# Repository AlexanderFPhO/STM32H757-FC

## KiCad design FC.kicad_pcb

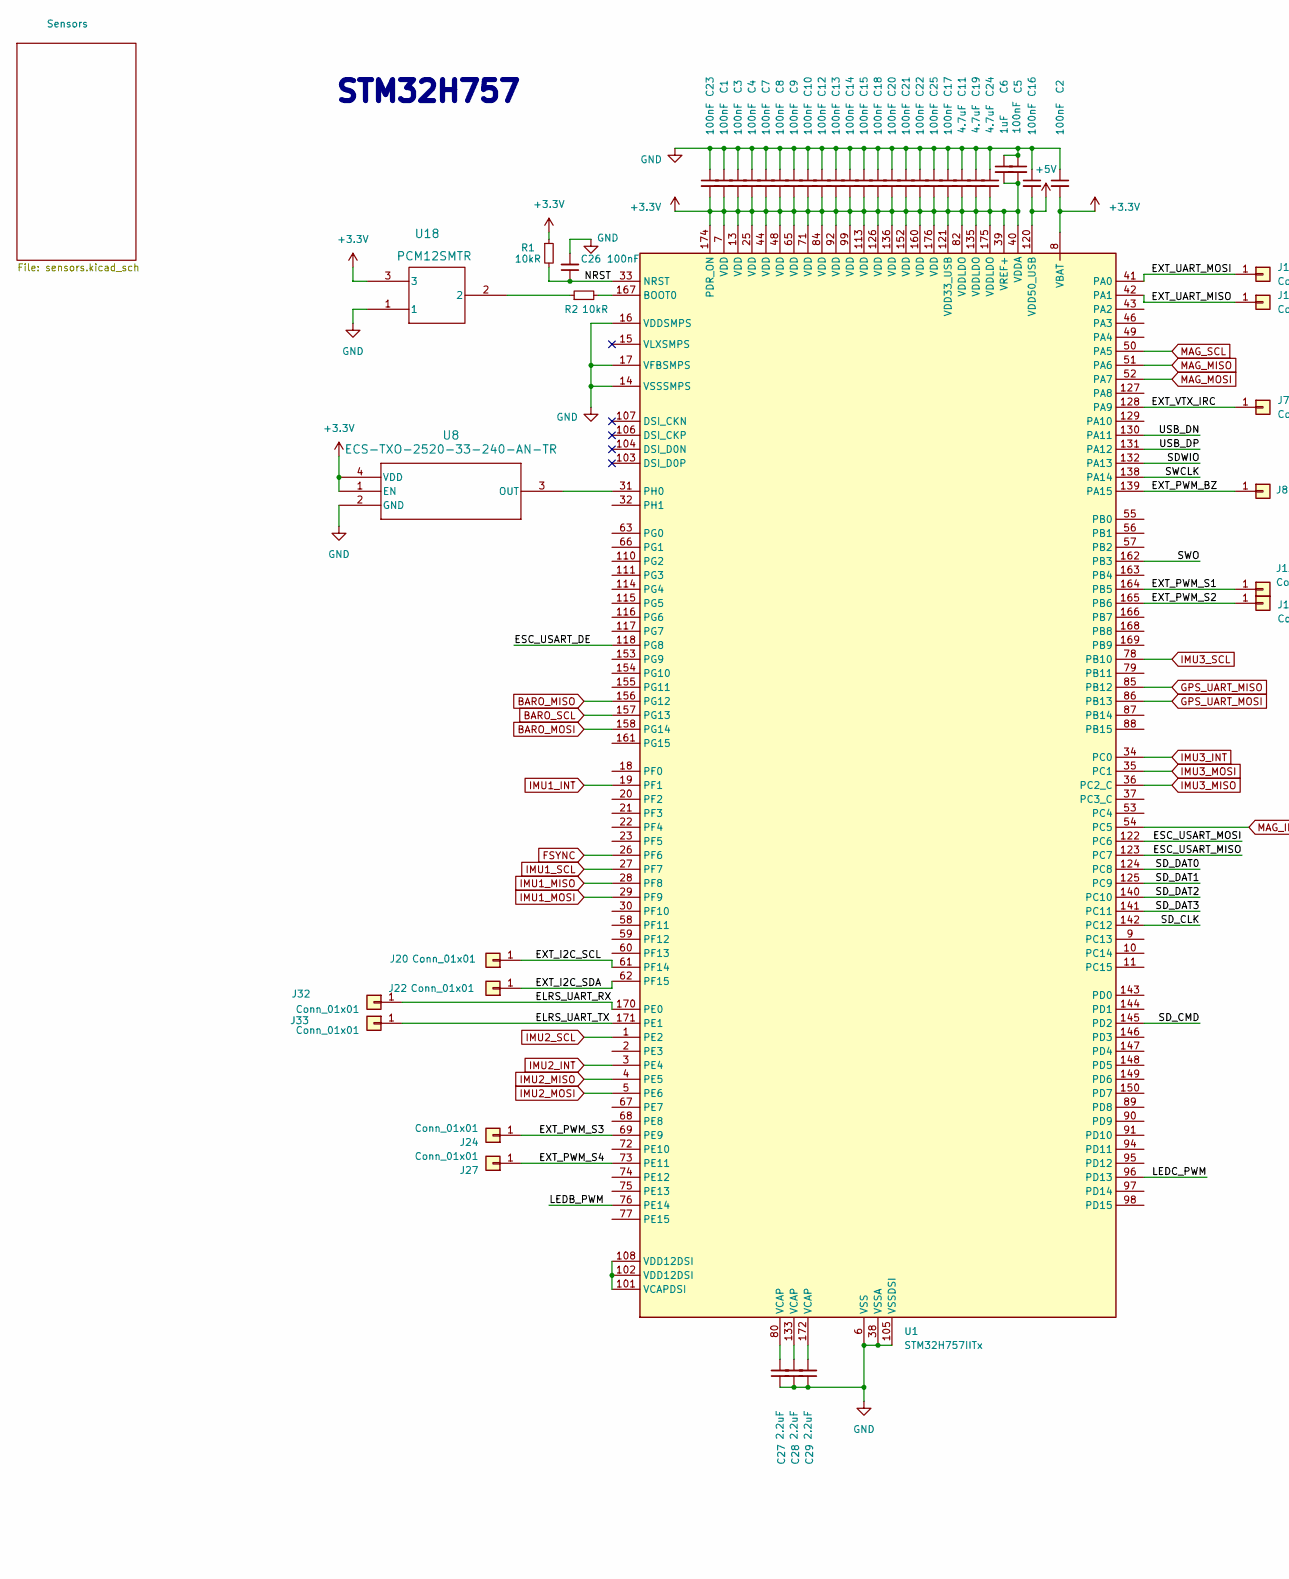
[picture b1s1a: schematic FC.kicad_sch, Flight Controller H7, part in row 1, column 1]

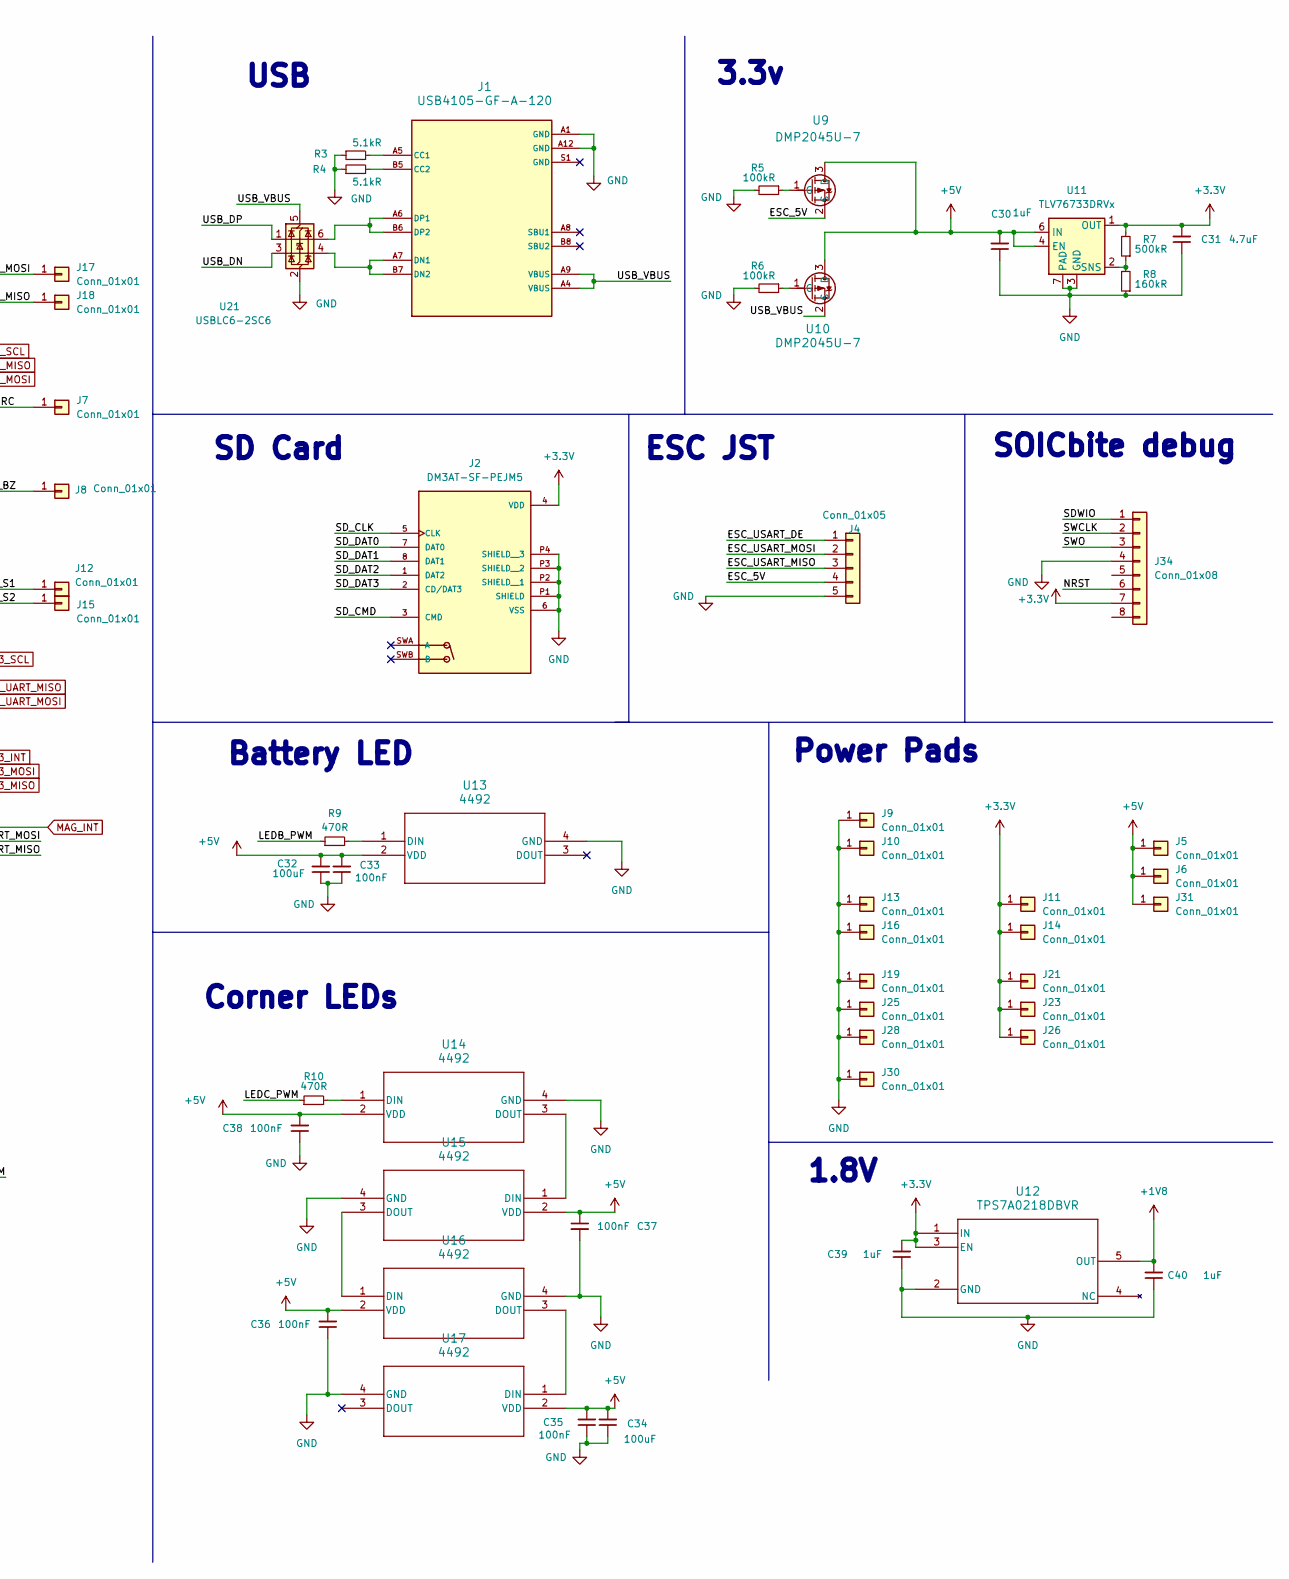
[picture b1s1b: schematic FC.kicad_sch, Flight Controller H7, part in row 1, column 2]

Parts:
C1, C2, C3, C4, C5, C7, C8, C9, C10, C12, C13, C14, C15, C16, C17, C18, C20, C21, C22, C23, C25, C26, C33, C35, C36, C37, C38: 100nF; C_0603_1608Metric
C6, C30, C39, C40: 1uF; C_0603_1608Metric
C11, C19, C24, C31: 4.7uF; C_0603_1608Metric
C27, C28, C29: 2.2uF; C_0603_1608Metric
C32, C34: 100uF; C_0805_2012Metric
J1: USB4105-GF-A-120; USB_C_Receptacle_GCT_USB4105-xx-A_16P_TopMnt_Horizontal_NOB
J2: DM3AT-SF-PEJM5; DM3AT-SF-PEJM5_HRS_DM3AT-SF-PEJM5; PARTREV 20200913
J4: Conn_01x05; JST_ZH_S5B-ZR-SM4A-TF_1x05-1MP_P1.50mm_Horizontal
J5, J6, J7, J8, J9, J10, J11, J12, J13, J14, J15, J16, J17, J18, J19, J20, J21, J22, J23, J24, J25, J26, J27, J28, J30, J31, J32, J33: Conn_01x01; WirePad_1x01_SMD_1.4x2mm
J34: Conn_01x08; SOIC_clipProgSmall
R1, R2: 10kR; R_0603_1608Metric
R3, R4: 5.1kR; R_0603_1608Metric
R5, R6: 100kR; R_0603_1608Metric
R7: 500kR; R_0603_1608Metric
R8: 160kR; R_0603_1608Metric
R9, R10: 470R; R_0603_1608Metric
U1: STM32H757IITx; LQFP-176_24x24mm_P0.5mm
U8: ECS-TXO-2520-33-240-AN-TR; ECS-TXO-2520-33-240-AN-TR_ECS
U9, U10: DMP2045U-7; SOT-23_DIO
U11: TLV76733DRVx; WSON-6-1EP_2x2mm_P0.65mm_EP1x1.6mm_ThermalVias
U12: TPS7A0218DBVR; SOT23_DBV_TEX
U13, U14, U15, U16, U17: 4492; 4492_ADA
U18: PCM12SMTR; PCM12SMTR_CNK
U21: USBLC6-2SC6; SOT-23-6

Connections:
+1V8: C40.2, U12.5 (OUT); also elsewhere on the board
+3.3V: C1.2, C2.2, C3.2, C4.2, C5.2, C6.2, C7.2, C8.2, C9.2, C10.2, C11.2, C12.2, C13.2, C14.2, C15.2, C17.2, C18.2, C19.2, C20.2, C21.2, C22.2, C23.2, C24.2, C25.2, C31.2, C39.2, J2.4 (VDD), J11.1, J14.1, J21.1, J23.1, J26.1, J34.7, R1.1, R7.2, U1.7 (VDD), U1.8 (VBAT), U1.13 (VDD), U1.25 (VDD), U1.39 (VREF+), U1.40 (VDDA), U1.44 (VDD), U1.48 (VDD), U1.65 (VDD), U1.71 (VDD), U1.82 (VDDLDO), U1.84 (VDD), U1.92 (VDD), U1.99 (VDD), U1.113 (VDD), U1.121 (VDD33_USB), U1.126 (VDD), U1.135 (VDDLDO), U1.136 (VDD), U1.152 (VDD), U1.160 (VDD), U1.174 (PDR_ON), U1.175 (VDDLDO), U1.176 (VDD), U8.1 (EN), U8.4 (VDD), U11.1 (OUT), U12.1 (IN), U12.3 (EN), U18.3; also elsewhere on the board
+5V: C16.2, C30.2, C32.2, C33.2, C34.2, C35.2, C36.2, C37.1, C38.2, J5.1, J6.1, J31.1, U1.120 (VDD50_USB), U9.3 (D), U10.3 (D), U11.4 (EN), U11.6 (IN), U13.2 (VDD), U14.2 (VDD), U15.2 (VDD), U16.2 (VDD), U17.2 (VDD)
/ELRS_UART_RX: J32.1, U1.170 (PE0)
/ELRS_UART_TX: J33.1, U1.171 (PE1)
/ESC_5V: J4.4, U9.2 (S)
/ESC_USART_DE: J4.1, U1.118 (PG8)
/ESC_USART_MISO: J4.3, U1.123 (PC7)
/ESC_USART_MOSI: J4.2, U1.122 (PC6)
/EXT_I2C_SCL: J20.1, U1.61 (PF14)
/EXT_I2C_SDA: J22.1, U1.62 (PF15)
/EXT_PWM_BZ: J8.1, U1.139 (PA15)
/EXT_PWM_S1: J12.1, U1.164 (PB5)
/EXT_PWM_S2: J15.1, U1.165 (PB6)
/EXT_PWM_S3: J24.1, U1.69 (PE9)
/EXT_PWM_S4: J27.1, U1.73 (PE11)
/EXT_UART_MISO: J18.1, U1.42 (PA1)
/EXT_UART_MOSI: J17.1, U1.41 (PA0)
/EXT_VTX_IRC: J7.1, U1.128 (PA9)
/LEDB_PWM: R9.1, U1.76 (PE14)
/LEDC_PWM: R10.1, U1.96 (PD13)
/NRST: C26.1, J34.6, R1.2, U1.33 (NRST)
/SDWIO: J34.1, U1.132 (PA13)
/SD_CLK: J2.5 (CLK), U1.142 (PC12)
/SD_CMD: J2.3 (CMD), U1.145 (PD2)
/SD_DAT0: J2.7 (DAT0), U1.124 (PC8)
/SD_DAT1: J2.8 (DAT1), U1.125 (PC9)
/SD_DAT2: J2.1 (DAT2), U1.140 (PC10)
/SD_DAT3: J2.2 (CD/DAT3), U1.141 (PC11)
/SWCLK: J34.2, U1.138 (PA14)
/SWO: J34.3, U1.162 (PB3)
/USB_DN: U1.130 (PA11), U21.3 (I/O2)
/USB_DP: U1.131 (PA12), U21.1 (I/O1)
/USB_VBUS: J1.A4 (VBUS), J1.A9 (VBUS), U10.2 (S), U21.5 (VBUS)
BARO_MISO: U1.156 (PG12); also elsewhere on the board
BARO_MOSI: U1.158 (PG14); also elsewhere on the board
BARO_SCL: U1.157 (PG13); also elsewhere on the board
FSYNC: U1.26 (PF6); also elsewhere on the board
GND: C1.1, C2.1, C3.1, C4.1, C5.1, C6.1, C7.1, C8.1, C9.1, C10.1, C11.1, C12.1, C13.1, C14.1, C15.1, C16.1, C17.1, C18.1, C19.1, C20.1, C21.1, C22.1, C23.1, C24.1, C25.1, C26.2, C27.1, C28.1, C29.1, C30.1, C31.1, C32.1, C33.1, C34.1, C35.1, C36.1, C37.2, C38.1, C39.1, C40.1, J1.A1 (GND), J1.A12 (GND), J2.6 (VSS), J2.P1 (SHIELD), J2.P2 (SHIELD__1), J2.P3 (SHIELD__2), J2.P4 (SHIELD__3), J4.5, J9.1, J10.1, J13.1, J16.1, J19.1, J25.1, J28.1, J30.1, J34.4, R3.1, R4.1, R5.2, R6.2, R8.1, U1.6 (VSS), U1.12 (VSS), U1.14 (VSSSMPS), U1.16 (VDDSMPS), U1.17 (VFBSMPS), U1.24 (VSS), U1.38 (VSSA), U1.45 (VSS), U1.47 (VSS), U1.64 (VSS), U1.70 (VSS), U1.81 (VSS), U1.83 (VSS), U1.93 (VSS), U1.100 (VSS), U1.105 (VSSDSI), U1.109 (VSSDSI), U1.112 (VSS), U1.119 (VSS), U1.134 (VSS), U1.137 (VSS), U1.151 (VSS), U1.159 (VSS), U1.173 (VSS), U8.2 (GND), U11.3 (GND), U11.5 (GND), U11.7 (PAD), U12.2 (GND), U13.4 (GND), U14.4 (GND), U15.4 (GND), U16.4 (GND), U17.4 (GND), U18.1, U21.2 (GND); also elsewhere on the board
GPS_UART_MISO: U1.85 (PB12); also elsewhere on the board
GPS_UART_MOSI: U1.86 (PB13); also elsewhere on the board
IMU1_INT: U1.19 (PF1); also elsewhere on the board
IMU1_MISO: U1.28 (PF8); also elsewhere on the board
IMU1_MOSI: U1.29 (PF9); also elsewhere on the board
IMU1_SCL: U1.27 (PF7); also elsewhere on the board
IMU2_INT: U1.3 (PE4); also elsewhere on the board
IMU2_MISO: U1.4 (PE5); also elsewhere on the board
IMU2_MOSI: U1.5 (PE6); also elsewhere on the board
IMU2_SCL: U1.1 (PE2); also elsewhere on the board
IMU3_INT: U1.34 (PC0); also elsewhere on the board
IMU3_MISO: U1.36 (PC2_C); also elsewhere on the board
IMU3_MOSI: U1.35 (PC1); also elsewhere on the board
IMU3_SCL: U1.78 (PB10); also elsewhere on the board
MAG_INT: U1.54 (PC5); also elsewhere on the board
MAG_MISO: U1.51 (PA6); also elsewhere on the board
MAG_MOSI: U1.52 (PA7); also elsewhere on the board
MAG_SCL: U1.50 (PA5); also elsewhere on the board
unnamed: C27.2, U1.80 (VCAP)
unnamed: C28.2, U1.133 (VCAP)
unnamed: C29.2, U1.172 (VCAP)
unnamed: J1.A5 (CC1), R3.2
unnamed: J1.B5 (CC2), R4.2
unnamed: J1.A7 (DN1), J1.B7 (DN2), U21.4 (I/O2)
unnamed: J1.A6 (DP1), J1.B6 (DP2), U21.6 (I/O1)
unnamed: R2.1, U18.2
unnamed: R2.2, U1.167 (BOOT0)
unnamed: U1.31 (PH0), U8.3 (OUT)
unnamed: U1.101 (VCAPDSI), U1.102 (VDD12DSI), U1.108 (VDD12DSI)
unnamed: R5.1, U9.1 (G)
unnamed: R6.1, U10.1 (G)
unnamed: R7.1, R8.2, U11.2 (SNS)
unnamed: R9.2, U13.1 (DIN)
unnamed: R10.2, U14.1 (DIN)
unnamed: U14.3 (DOUT), U15.1 (DIN)
unnamed: U15.3 (DOUT), U16.1 (DIN)
unnamed: U16.3 (DOUT), U17.1 (DIN)

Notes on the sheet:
ESC JST
USB
Corner LEDs
1.8V
SOICbite debug
Power Pads
Battery LED
SD Card
STM32H757
3.3v

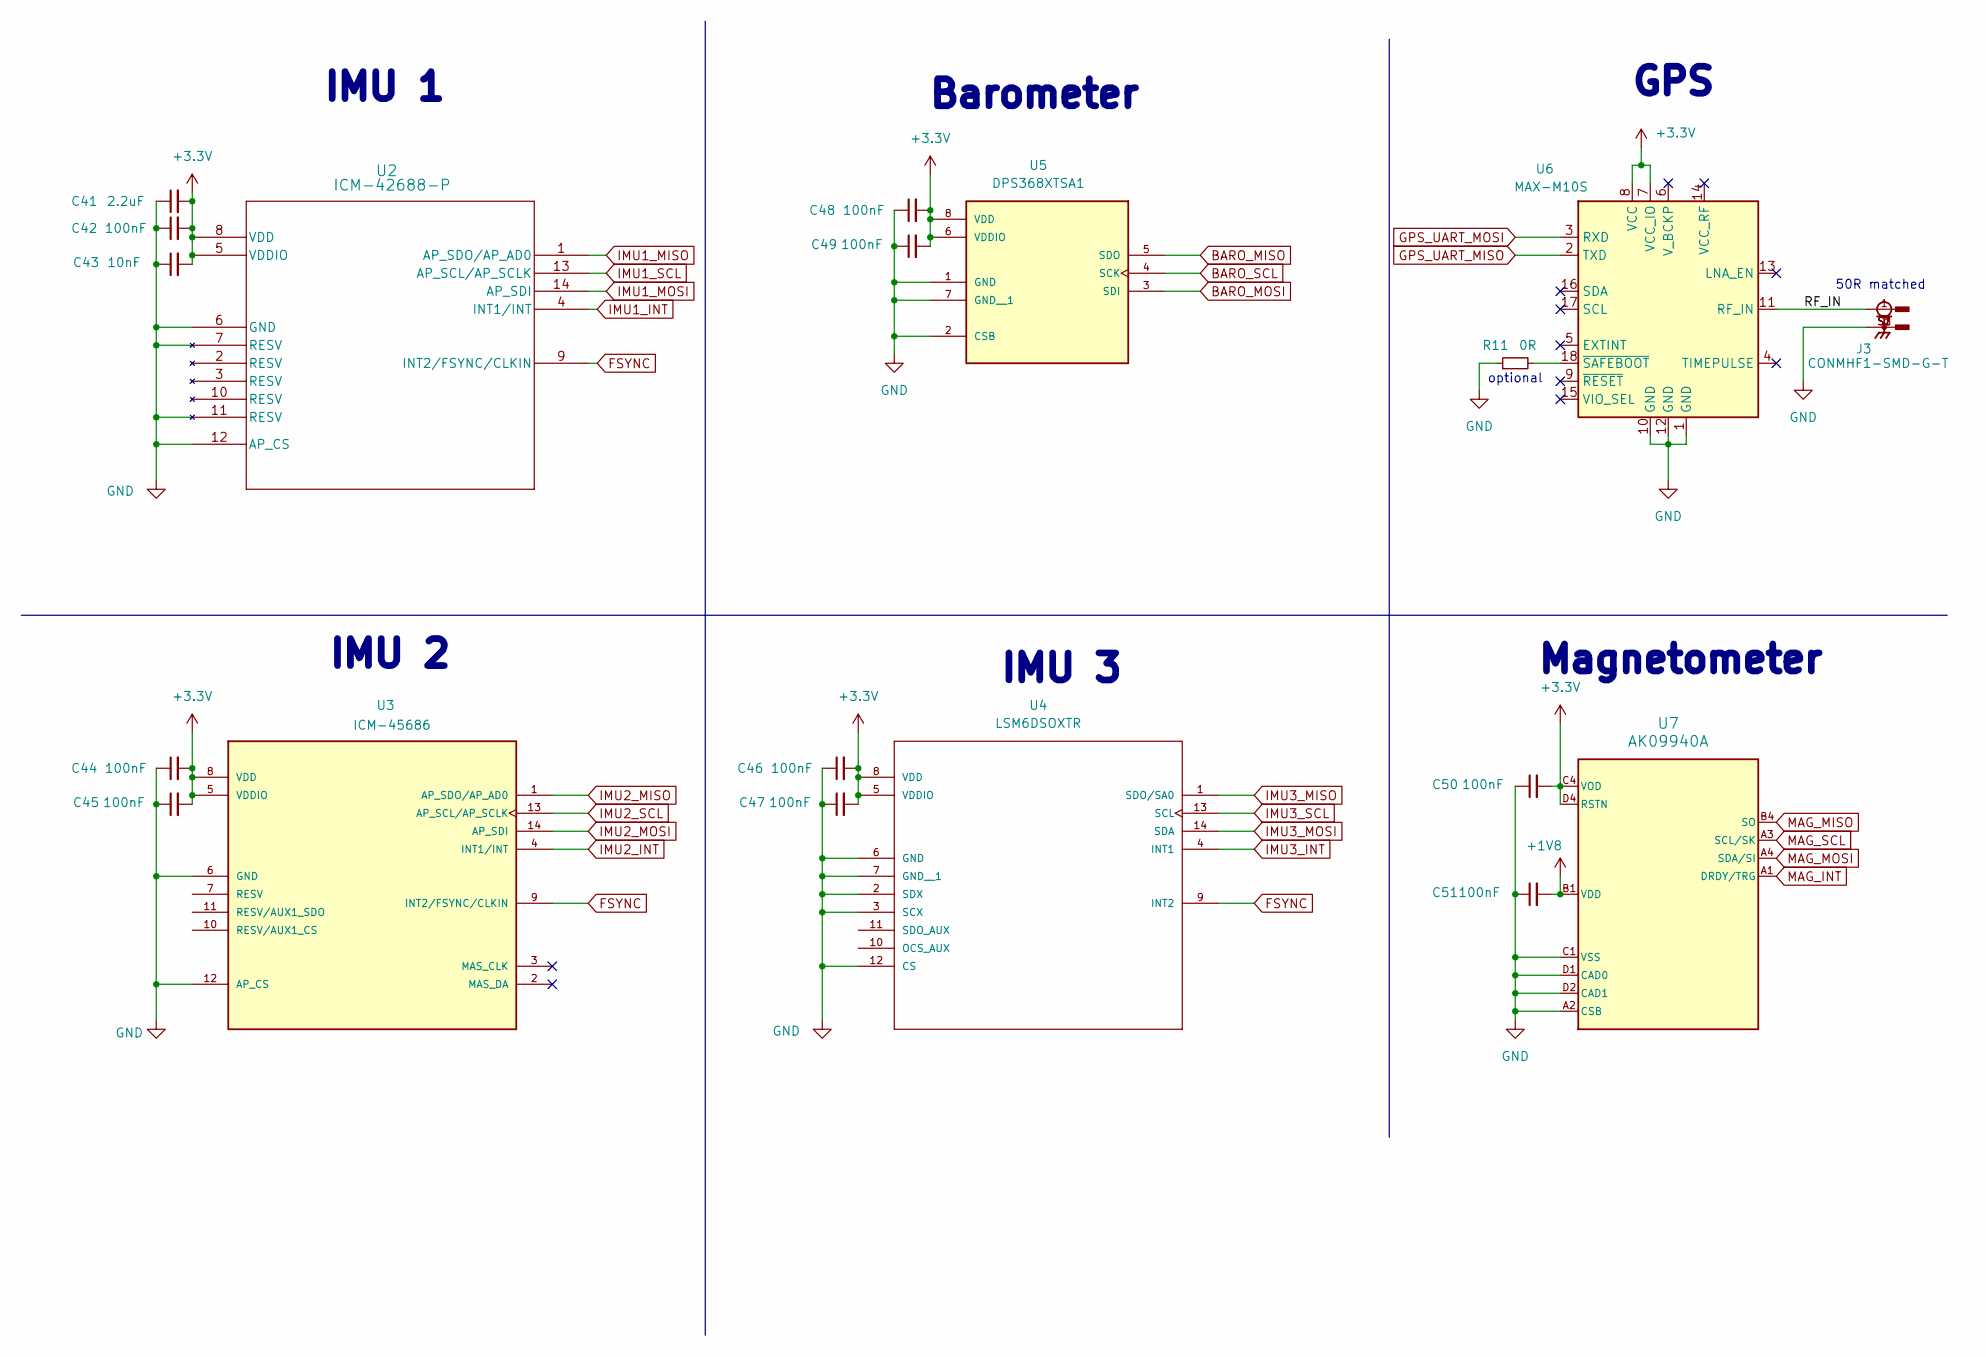
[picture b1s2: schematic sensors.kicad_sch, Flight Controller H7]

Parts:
C41: 2.2uF; C_0603_1608Metric
C42, C44, C45, C46, C47, C48, C49, C50, C51: 100nF; C_0603_1608Metric
C43: 10nF; C_0603_1608Metric
J3: CONMHF1-SMD-G-T; CONMHF1-SMD-G-T_LINX_CONMHF1-SMD-G-T
R11: 0R; R_0603_1608Metric
U2: ICM-42688-P; LGA14_2P5X3X0P91_TDK
U3: ICM-45686; ICM-45686_IC_ICM-45686; PARTREV 0.2
U4: LSM6DSOXTR; LSM6DSOXTR_PQFN50P250X300X86-14N; PARTREV 3.0
U5: DPS368XTSA1; DPS368XTSA1_XDCR_DPS368XTSA1
U6: MAX-M10S; ublox_MAX
U7: AK09940A; LGA11_1p6x1p6x0p58_AKM

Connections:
+1V8: C51.2, U7.B1 (VDD); also elsewhere on the board
+3.3V: C41.2, C42.2, C43.2, C44.2, C45.2, C46.2, C47.2, C48.2, C49.2, C50.2, U2.5 (VDDIO), U2.8 (VDD), U3.5 (VDDIO), U3.8 (VDD), U4.5 (VDDIO), U4.8 (VDD), U5.6 (VDDIO), U5.8 (VDD), U6.7 (VCC_IO), U6.8 (VCC), U7.C4 (VOD), U7.D4 (RSTN); also elsewhere on the board
/Sensors/RF_IN: J3.1, U6.11 (RF_IN)
BARO_MISO: U5.5 (SDO); also elsewhere on the board
BARO_MOSI: U5.3 (SDI); also elsewhere on the board
BARO_SCL: U5.4 (SCK); also elsewhere on the board
FSYNC: U2.9 (INT2/FSYNC/CLKIN), U3.9 (INT2/FSYNC/CLKIN), U4.9 (INT2); also elsewhere on the board
GND: C41.1, C42.1, C43.1, C44.1, C45.1, C46.1, C47.1, C48.1, C49.1, C50.1, C51.1, J3.S1, J3.S2, J3.S3, R11.1, U2.6 (GND), U2.7 (RESV), U2.11 (RESV), U2.12 (AP_CS), U3.6 (GND), U3.12 (AP_CS), U4.2 (SDX), U4.3 (SCX), U4.6 (GND), U4.7 (GND__1), U4.12 (CS), U5.1 (GND), U5.2 (CSB), U5.7 (GND__1), U6.1 (GND), U6.10 (GND), U6.12 (GND), U7.A2 (CSB), U7.C1 (VSS), U7.D1 (CAD0), U7.D2 (CAD1); also elsewhere on the board
GPS_UART_MISO: U6.2 (TXD); also elsewhere on the board
GPS_UART_MOSI: U6.3 (RXD); also elsewhere on the board
IMU1_INT: U2.4 (INT1/INT); also elsewhere on the board
IMU1_MISO: U2.1 (AP_SDO/AP_AD0); also elsewhere on the board
IMU1_MOSI: U2.14 (AP_SDI); also elsewhere on the board
IMU1_SCL: U2.13 (AP_SCL/AP_SCLK); also elsewhere on the board
IMU2_INT: U3.4 (INT1/INT); also elsewhere on the board
IMU2_MISO: U3.1 (AP_SDO/AP_AD0); also elsewhere on the board
IMU2_MOSI: U3.14 (AP_SDI); also elsewhere on the board
IMU2_SCL: U3.13 (AP_SCL/AP_SCLK); also elsewhere on the board
IMU3_INT: U4.4 (INT1); also elsewhere on the board
IMU3_MISO: U4.1 (SDO/SA0); also elsewhere on the board
IMU3_MOSI: U4.14 (SDA); also elsewhere on the board
IMU3_SCL: U4.13 (SCL); also elsewhere on the board
MAG_INT: U7.A1 (DRDY/TRG); also elsewhere on the board
MAG_MISO: U7.B4 (SO); also elsewhere on the board
MAG_MOSI: U7.A4 (SDA/SI); also elsewhere on the board
MAG_SCL: U7.A3 (SCL/SK); also elsewhere on the board
unnamed: R11.2, U6.18 (~SAFEBOOT)

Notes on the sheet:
Magnetometer
IMU 3
Barometer
50R matched
IMU 2
optional
IMU 1
GPS

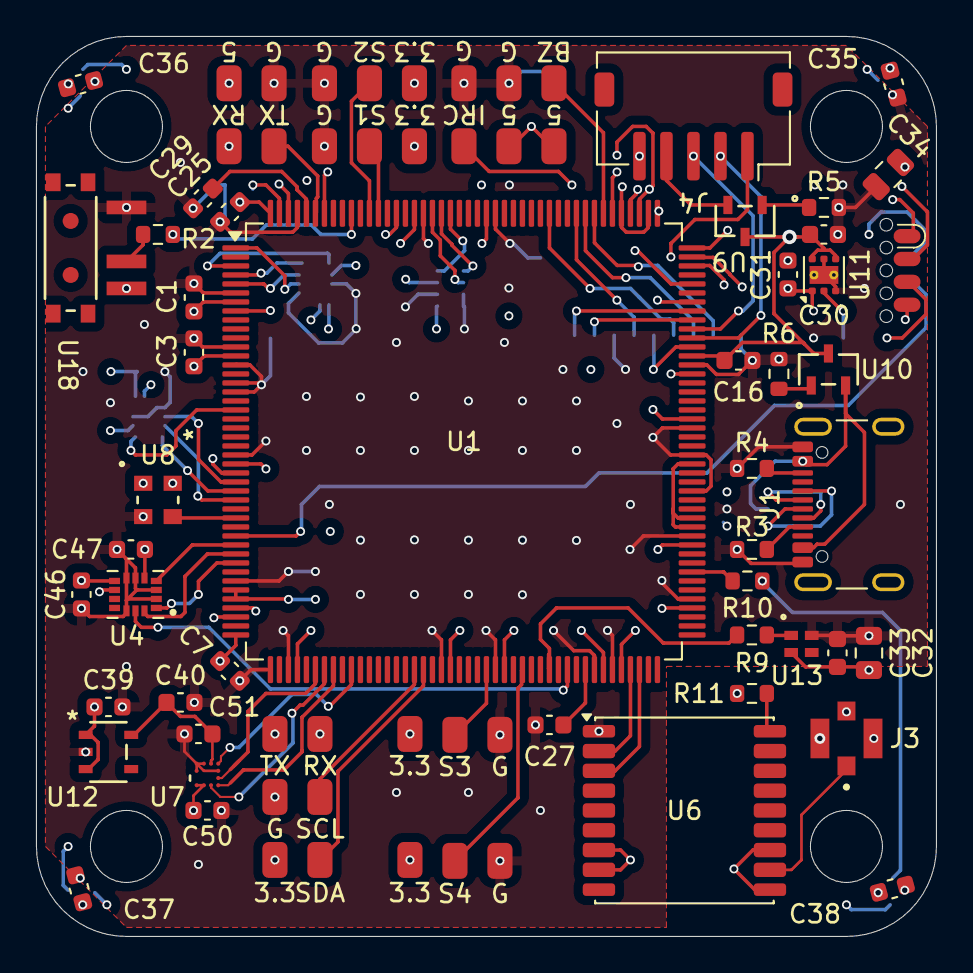
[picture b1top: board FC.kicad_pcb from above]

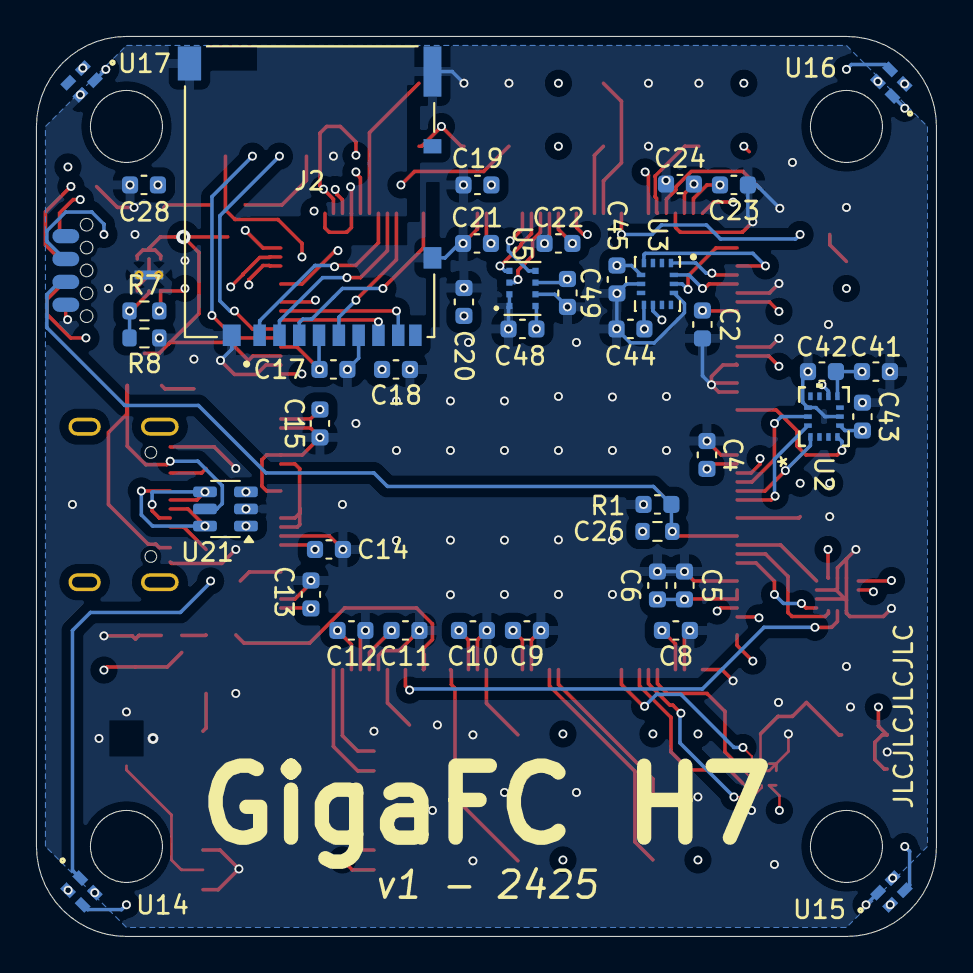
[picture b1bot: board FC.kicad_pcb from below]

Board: 6 copper layers, 50.0 x 50.0 mm, 114 parts (41 on the bottom side), 78 nets.

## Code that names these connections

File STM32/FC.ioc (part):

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Mcu.Name=STM32H757IITx
Mcu.Package=LQFP176
Mcu.UserName=STM32H757IITx
PA0.GPIOParameters=PinAttribute
PA0.Mode=Asynchronous
PA0.PinAttribute=CortexM7
PA0.Signal=UART4_TX
PA1.GPIOParameters=PinAttribute
PA1.Mode=Asynchronous
PA1.PinAttribute=CortexM7
PA1.Signal=UART4_RX
PA10.GPIOParameters=PinAttribute
PA10.Mode=Asynchronous
PA10.PinAttribute=CortexM4
PA10.Signal=LPUART1_RX
PA11.GPIOParameters=PinAttribute
PA11.Mode=Device_Only
PA11.PinAttribute=CortexM7
PA11.Signal=USB_OTG_FS_DM
PA12.GPIOParameters=PinAttribute
PA12.Mode=Device_Only
PA12.PinAttribute=CortexM7
PA12.Signal=USB_OTG_FS_DP
PA13\ (JTMS/SWDIO).GPIOParameters=PinAttribute
PA13\ (JTMS/SWDIO).Mode=Trace_Asynchronous_SW
PA13\ (JTMS/SWDIO).PinAttribute=CortexM7
PA13\ (JTMS/SWDIO).Signal=DEBUG_JTMS-SWDIO
PA14\ (JTCK/SWCLK).GPIOParameters=PinAttribute
PA14\ (JTCK/SWCLK).Mode=Trace_Asynchronous_SW
PA14\ (JTCK/SWCLK).PinAttribute=CortexM7
PA14\ (JTCK/SWCLK).Signal=DEBUG_JTCK-SWCLK
PA15\ (JTDI).GPIOParameters=PinAttribute
PA15\ (JTDI).PinAttribute=CortexM4
PA15\ (JTDI).Signal=S_TIM2_CH1_ETR
PA5.GPIOParameters=PinAttribute
PA5.Mode=Full_Duplex_Master
PA5.PinAttribute=CortexM7
PA5.Signal=SPI1_SCK
PA6.GPIOParameters=PinAttribute
PA6.Mode=Full_Duplex_Master
PA6.PinAttribute=CortexM7
PA6.Signal=SPI1_MISO
PA7.GPIOParameters=PinAttribute
PA7.Mode=Full_Duplex_Master
PA7.PinAttribute=CortexM7
PA7.Signal=SPI1_MOSI
PA9.GPIOParameters=PinAttribute
PA9.Mode=Asynchronous
PA9.PinAttribute=CortexM4
PA9.Signal=LPUART1_TX
PB10.GPIOParameters=PinAttribute
PB10.Mode=Full_Duplex_Master
PB10.PinAttribute=CortexM7
PB10.Signal=SPI2_SCK
PB12.GPIOParameters=PinAttribute
PB12.Mode=Asynchronous
PB12.PinAttribute=CortexM4
PB12.Signal=UART5_RX
PB13.GPIOParameters=PinAttribute
PB13.Mode=Asynchronous
PB13.PinAttribute=CortexM4
PB13.Signal=UART5_TX
PB3\ (JTDO/TRACESWO).GPIOParameters=PinAttribute
PB3\ (JTDO/TRACESWO).Mode=Trace_Asynchronous_SW
PB3\ (JTDO/TRACESWO).PinAttribute=CortexM7
PB3\ (JTDO/TRACESWO).Signal=DEBUG_JTDO-SWO
PB5.GPIOParameters=PinAttribute
PB5.PinAttribute=CortexM4
PB5.Signal=S_TIM3_CH2
PB6.GPIOParameters=PinAttribute
PB6.PinAttribute=CortexM4
PB6.Signal=S_TIM4_CH1
PB8.GPIOParameters=PinAttribute
PB8.PinAttribute=CortexM4
PB8.Signal=S_TIM4_CH3
PC0.GPIOParameters=PinAttribute
PC0.PinAttribute=Free
PC0.Signal=GPXTI0
PC1.GPIOParameters=PinAttribute
PC1.Mode=Full_Duplex_Master
PC1.PinAttribute=CortexM7
PC1.Signal=SPI2_MOSI
PC10.GPIOParameters=PinAttribute
PC10.Mode=SD_4_bits_Wide_bus
PC10.PinAttribute=CortexM4
PC10.Signal=SDMMC1_D2
PC11.GPIOParameters=PinAttribute
PC11.Mode=SD_4_bits_Wide_bus
PC11.PinAttribute=CortexM4
PC11.Signal=SDMMC1_D3
PC12.GPIOParameters=PinAttribute
PC12.Mode=SD_4_bits_Wide_bus
PC12.PinAttribute=CortexM4
PC12.Signal=SDMMC1_CK
PC2_C.GPIOParameters=PinAttribute
PC2_C.Mode=Full_Duplex_Master
PC2_C.PinAttribute=CortexM7
PC2_C.Signal=SPI2_MISO
PC5.GPIOParameters=PinAttribute
PC5.PinAttribute=Free
PC5.Signal=GPXTI5
PC6.GPIOParameters=PinAttribute
PC6.Mode=Asynchronous
PC6.PinAttribute=CortexM7
PC6.Signal=USART6_TX
PC7.GPIOParameters=PinAttribute
PC7.Mode=Asynchronous
PC7.PinAttribute=CortexM7
PC7.Signal=USART6_RX
PC8.GPIOParameters=PinAttribute
PC8.Mode=SD_4_bits_Wide_bus
PC8.PinAttribute=CortexM4
PC8.Signal=SDMMC1_D0
PC9.GPIOParameters=PinAttribute
PC9.Mode=SD_4_bits_Wide_bus
PC9.PinAttribute=CortexM4
PC9.Signal=SDMMC1_D1
PD13.GPIOParameters=PinAttribute
PD13.PinAttribute=CortexM4
PD13.Signal=S_TIM4_CH2
PD2.GPIOParameters=PinAttribute
PD2.Mode=SD_4_bits_Wide_bus
PD2.PinAttribute=CortexM4
PD2.Signal=SDMMC1_CMD
PE0.GPIOParameters=PinAttribute
PE0.Mode=Asynchronous
PE0.PinAttribute=CortexM7
PE0.Signal=UART8_RX
PE1.GPIOParameters=PinAttribute
PE1.Mode=Asynchronous
PE1.PinAttribute=CortexM7
PE1.Signal=UART8_TX
PE11.GPIOParameters=PinAttribute
PE11.PinAttribute=CortexM4
PE11.Signal=S_TIM1_CH2
PE14.GPIOParameters=PinAttribute
PE14.PinAttribute=CortexM4
PE14.Signal=S_TIM1_CH4
PE2.GPIOParameters=PinAttribute
PE2.Mode=Full_Duplex_Master
PE2.PinAttribute=CortexM7
PE2.Signal=SPI4_SCK
PE4.GPIOParameters=PinAttribute
PE4.PinAttribute=Free
PE4.Signal=GPXTI4
PE5.GPIOParameters=PinAttribute
PE5.Mode=Full_Duplex_Master
PE5.PinAttribute=CortexM7
PE5.Signal=SPI4_MISO
PE6.GPIOParameters=PinAttribute
PE6.Mode=Full_Duplex_Master
PE6.PinAttribute=CortexM7
PE6.Signal=SPI4_MOSI
PE9.GPIOParameters=PinAttribute
PE9.PinAttribute=CortexM4
PE9.Signal=S_TIM1_CH1
PF1.GPIOParameters=PinAttribute
PF1.PinAttribute=Free
PF1.Signal=GPXTI1
PF14.GPIOParameters=PinAttribute
PF14.Mode=I2C
PF14.PinAttribute=CortexM7
PF14.Signal=I2C4_SCL
PF15.GPIOParameters=PinAttribute
PF15.Mode=I2C
PF15.PinAttribute=CortexM7
PF15.Signal=I2C4_SDA
PF6.GPIOParameters=PinAttribute
PF6.PinAttribute=CortexM4
PF6.Signal=S_TIM16_CH1
PF7.GPIOParameters=PinAttribute
PF7.Mode=Full_Duplex_Master
PF7.PinAttribute=CortexM7
PF7.Signal=SPI5_SCK
PF8.GPIOParameters=PinAttribute
PF8.Mode=Full_Duplex_Master
PF8.PinAttribute=CortexM7
PF8.Signal=SPI5_MISO
PF9.GPIOParameters=PinAttribute
PF9.Mode=Full_Duplex_Master
PF9.PinAttribute=CortexM7
PF9.Signal=SPI5_MOSI
PG12.GPIOParameters=PinAttribute
PG12.Mode=Full_Duplex_Master
PG12.PinAttribute=CortexM7
PG12.Signal=SPI6_MISO
PG13.GPIOParameters=PinAttribute
PG13.Mode=Full_Duplex_Master
PG13.PinAttribute=CortexM7
PG13.Signal=SPI6_SCK
PG14.GPIOParameters=PinAttribute
PG14.Mode=Full_Duplex_Master
PG14.PinAttribute=CortexM7
PG14.Signal=SPI6_MOSI
PG8.GPIOParameters=PinAttribute
PG8.Mode=Hardware Flow Control (RS485)
PG8.PinAttribute=CortexM7
PG8.Signal=USART6_DE
PH0-OSC_IN\ (PH0).GPIOParameters=PinAttribute
PH0-OSC_IN\ (PH0).Mode=HSE-External-Clock-Source
PH0-OSC_IN\ (PH0).PinAttribute=Free
PH0-OSC_IN\ (PH0).Signal=RCC_OSC_IN
RCC.SYSCLKFreq_VALUE=480000000
RCC.SYSCLKSource=RCC_SYSCLKSOURCE_PLLCLK
board=custom

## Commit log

2025-06-04 remove old files
2025-06-07 V2 with feedback
2025-06-09 V1 manufacturing
2025-06-13 A few changes for v1 manufacturing and STMCubeMX generation
